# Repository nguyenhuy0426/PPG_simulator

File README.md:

# 🫀 PPG Signal Simulator — Raspberry Pi 4

**Dual-channel PPG research simulator with Raspberry Pi software, three KiCad 10 boards and a printable optical enclosure.**

**Group #2:** HuyNN, VyPT
**Institution:** Industrial University of Ho Chi Minh City (IUH) — Faculty of Electronic Technology
**Version:** 5.0.0 — waveform controls and timestamped recording

---

## 📋 Overview

The Raspberry Pi runtime synthesizes IR/RED signals at 100 Hz, interpolates them
for a nominal 500 Hz dual-MCP4725 output on ARM64, and acquires OPT101 signals separately.
`PPG_DAC_RATE_HZ` supports 100/200/500/1000 Hz; desktop default is 1000 Hz.
Pi GUI + BLE + A0 verification at 500 Hz completed 30 seconds without buffer
overruns or dropped samples. Optical waveform fidelity is still unverified.
The empirical SpO₂ mapping is configurable; a realistic plot does not establish
optical accuracy or compatibility with a particular pulse oximeter.

**Touch and sequence update (30 September 2026):** Numeric controls use sliders;
Settings and calibration include −/+ fine steps. **04 PPG morphology** offers
fitted Gaussian and an exploratory **LSM-GAN 30-second sequence**, a real training
reference, and a live **OPT101 RX** card (A0/A4).
Play/Stop uses the shared MCP4725 writer; clips stop at 30 seconds or when leaving
the page. Opening the page does not emit output. Classic Gaussian is preserved.

LSM keeps native 40 Hz timing and has no HR/notch conditioning. The existing v2
checkpoint has excessive beat variability relative to median validation data;
it is a development baseline, not a validated human-PPG replacement. IR/RED share
one shape with nominal scaling. See [architecture choice, measured sequence audit
and touch/output details](docs/ppg_touch_sequence_output_2026-09-30.md).
The [earlier morphology comparison](docs/ppg_morphology_selection_2026-09-28.md)
remains a historical exploratory result; test has already been viewed.

**RX beside TX & Bench Diagnostics (October 2026):**
- **Live A0/A4 RX card on every page:** Classic, Calibration, Recordings and PPG morphology each show a read-only RX card next to the TX plot (the earlier bottom dock, and the RX strip inside the Signal setup window, are removed). It displays the rolling 8-second window of raw ADC mV at up to 10 Hz refresh, with explicit status states (disabled, dry-run, stale, error, full-scale) and touch-optimized scrolling on 1024×600 screens ([docs/rx-monitor-2026-10-01.md](docs/rx-monitor-2026-10-01.md)).
- **Physical Sensor Diagnostic Protocol:** A bench test and signal conditioning plan is established for OPT101 / CJMCU-101 modules, covering internal 1 MΩ feedback verification, 3.3 V Grove Hat input limits, dark readings, stepped sine wave tests (1–10 Hz), and RC low-pass filtering at $f_c \approx 33.9\text{ Hz}$ ([docs/opt101-a0-diagnostic-2026-10-01.md](docs/opt101-a0-diagnostic-2026-10-01.md)).

| Live monitor | Waveform setup | 30-second sequence |
|---|---|---|
|  |  |  |

### What's complete in v5

- Light controls, charcoal IR/RED plots, large setpoints and timestamp axes. The UI scales automatically from compact 7-inch 1024×600 panels through Full-HD/QHD desktop displays.
- HR 10–300 bpm; respiration 1–150 brpm; SpO₂ target 0–100%; PI convenience input 0.01–30%.
- Independent IR/RED AC and DC, AC/DC ownership, output offset, gain and polarity.
- PPG, sine, triangle and square waveforms; independent SP/DN/DP timing for each channel.
- Baseline, amplitude and frequency respiratory modulation, inhale/exhale ratio, per-channel variation and periodic apnea.
- Absolute-mV artefacts with optional seeds; configurable HR/amplitude, SpO₂/notch and beat-variability effects.
- Timestamped 100 Hz model-command CSV recording continues across pages; playback follows the recorded timestamps.
- Explicit Start/Stop for calibration; only the engine's DAC thread produces its sine output.
- Configuration round-trip, validation and atomic JSON save. Opening a page does not change signal parameters.
- English/Vietnamese UI; touch-sized controls; TX on the left and live OPT101 A0/A4 RX on the right of every page.
- Collapsible left navigation rail (icons collapsed, labels overlay when expanded), light/dark theme saved in `config.json`, and a Classic page with TX and RX side by side. The status line reports *no MCP4725 at 0x60/0x61* instead of claiming LED output when the DACs do not answer.
- `scripts/deploy_and_run.sh` (run on the laptop): SSH check, `i2cdetect -y 1` report for 0x08/0x60/0x61, rsync to the Pi, restart the app on the Pi display (the autostart user service when it is installed), and a dry-run copy on the laptop. When the Ethernet link reports `NO-CARRIER`, use the Wi‑Fi address: `PI_HOST=user@<pi-wifi-ip> scripts/deploy_and_run.sh`, and stop any other running instance first so two apps do not share I2C/BLE.

See [the continuation and validation report](docs/phase_reports/V5_CONTINUATION_REPORT.md)
for scope, evidence, commercial-reference comparison and physical validation still needed.

### Neural waveform models

The app's Neural page offers the fitted three-Gaussian shaper and the LSM-GAN sequence (normalized 30 s strip at 40 Hz,
BIDMC, no rate control, no paired IR/RED, no calibrated SpO₂); `assets/neural/manifest.json` lists the packaged files.

PhysioMix (round 9) and PhysioFlow (round 10) were removed from the app with every research generator that did not
improve on them. A strict real-vs-generated judge retrained per source on unseen people (C2ST, validation AUC; 0.5 =
indistinguishable, the real-vs-real control is about 0.45) still separated them at 0.99–1.00, as it did PhysioMix with
the strict critic, LSM-GAN-S, the flow-GANs G1–G3, BeatGen and the spectral-finish variants (0.95–1.00). Kept for
further work: PhysioFlow-R (R1, mean 0.759 over seeds 0.745–0.785 at 16 Heun steps, the only clear gain), its fine-tune R1F and PhysioGAN-R
(P5, in training), and the LSM-GAN author topology as the unchanged baseline. The removed models' results stay in
`ml/runs`, [docs/model-report](docs/model-report/README.md) and [docs/physioflow/REPORT_VI.md](docs/physioflow/REPORT_VI.md);
their code is in git history. These are engineering evaluations of normalized waveform shape, not clinical
validation, and they were not measured on the Pi/DAC/OPT101.

PPG-physiGPT (`ml/kaggle_physigpt/`, research only, not in the app) is an unconditional GPT-PPG-style patch
transformer with a flow-matching head, pretrained on MIMIC-III WDB on Kaggle 2 x T4. The strict judge still separates
every variant (AUC 1.0). On a second, feature-level tier (1 - KS over 14 waveform features against unseen people),
the 99.9M large model reaches 0.941 against 0.933 for the best 30.7M base, where real people score 0.960. It is the
V1 release: V1 asks for 95% of the real-vs-real similarity (large: 98.1%). The V2 target, absolute 0.95 with a
feature-only tree classifier at most 0.60 accurate (large: 0.618), is not met; the gap left is 5-8 Hz detail. Results and run records: [docs/physigpt](docs/physigpt/README.md).

#### Earlier models (history)

The **04 PPG morphology** page keeps the original three-Gaussian
generator and offers the LSM-GAN sequence as an experimental model. The
cWGAN-GP checkpoint below is retained for research comparison; it is not the
current sequence source. Both neural models were trained from BIDMC 1.0.0 PPG
records using subject-separated train/validation/test groups. They do not learn
separate IR and RED optical channels.

| Model | What goes in → what comes out | Network idea | Current role |
|---|---|---|---|
| cWGAN-GP pilot | 32-value random latent vector + 7 measured morphology conditions → one 256-point, phase-normalized pulse | Dense layers followed by three linear-upsample/Conv1D stages; strided-convolution critic; Wasserstein loss with gradient penalty | Research artifact only; the pilot export contains G but not its trained critic. The app's older preview repeated this one pulse to form a longer trace. |
| LSM-GAN v2 | A random 1,200-point noise strip → 1,200 PPG samples, 30 s at 40 Hz | Generator has parallel Conv1D branches (kernels 5/21/61) and a spectral-matching objective; its discriminator is a CNN with two real/fake scores | Experimental long-sequence option in page 04; no HR/notch control. |

For LSM-GAN, training used 624 non-overlapping 30-second windows from 32
patients; validation and test each used 112 windows from 7 separate patients.
BIDMC's 125 Hz signals were resampled to 40 Hz, filtered at 0.9–5 Hz and
normalized per window. This is not raw, full-band PPG or a healthy-population
dataset. The model produces a normalized shape; the app maps that shape to
nominal IR/RED voltage levels, so it does not predict two independently learned
optical signals or calibrated SpO₂.

These experiments are **exploratory** because the test set had already been
viewed. cWGAN makes a single pulse while LSM-GAN makes a long sequence, so
their scores are not a fully like-for-like ranking. Selection considers the
pre-agreed spectrum similarity, autocorrelation and high-frequency energy;
loss and discriminator scores alone are not evidence of realistic PPG.
See the [detailed LSM/GAN report](docs/ppg_lsm_gan_report_2026-09-26.md),
[cWGAN and LSM integration audit](docs/ppg_neural_preview_report_2026-09-28.md)
and [current sequence and hardware validation](docs/ppg_touch_sequence_output_2026-09-30.md).

### Key Specifications

| Parameter               | Value                                           |
|------------------------|-------------------------------------------------|
| Platform               | Raspberry Pi 4 (Ubuntu 24.04/26.04 LTS, arm64)  |
| UI Library             | CustomTkinter                                   |
| DAC                    | MCP4725 (12-bit, I2C) × 2 — IR & Red channels   |
| Model Rate             | 100 Hz                                          |
| DAC Rate               | Pi: 500 Hz target; configurable; Linux/I²C timing requires measurement |
| Data Recording         | 100 Hz model commands, timestamped CSV in `dataset/` |
| DAC Voltage Range      | Configured 0–3.28 V (0 → 0, 3.28 V → 4095) |
| Live RX ADC Channels   | A4 (IR) & A0 (Red) on Grove Base Hat (I2C 0x08) |

---

## 🛠️ Hardware Architecture

### Pin Mapping (Raspberry Pi 4, BCM numbering)

```
MCP4725 DACs (I2C Bus 1):
  GPIO2 (pin 3)   → I2C1_SDA
  GPIO3 (pin 5)   → I2C1_SCL
  Addresses: 0x61 (IR channel), 0x60 (Red channel)

Display:
  HDMI → Any screen (auto-detect resolution)
```

### Official KiCad PCB design

The official panel contains **two electrically independent boards**: the
70 × 20 mm OPT101 receiver and the 70 × 40 mm LED/IR driver. The 70 × 60 mm
panel has one V-score at 20 mm from the top. BPW34 remains available as a
separate historical alternative and is not part of this panel.

- [Two-board panel and build instructions](hardware/ppg_panel/README.md)
- [LED/IR driver schematic, PCB and wiring](hardware/led_ir_driver/README.md)
- [OPT101 receiver](hardware/opt101_receiver_kicad/opt101_receiver/README.md)
- [BPW34 receiver (alternative)](hardware/bpw34_receiver/README.md)

The driver uses a single shared I²C connection: J2 pins 3–6 are SCL, SDA,
3.3 V and GND. Both MCP4725 modules share that bus; configure different
addresses (IR 0x60 and RED 0x61). J2 pins 1–2 are the IR DAC output and GND,
not part of the four-wire I²C cable. J2 uses a 2.54 mm 1×2 header and a
separate 2.00 mm 1×4 header. There are no J8/J9 I²C headers or R11–R14 /
JP1–JP4 I²C options on this design. See the driver README before wiring.

This restores the earlier shared-bus driver; later v2.0 manufacturing-rule
changes are not incorporated. Existing three-board panel and v2.0 driver
fabrication files are obsolete and have been removed. Recheck board-house
requirements and regenerate Gerber/drill files before ordering. CAD checks do
not establish physical operation.

### Printable optical enclosure

The dark chamber has separate RED/IR lanes, a sliding LED carrier, replaceable
apertures, a labyrinth lid and cable passages. The parametric model and assembly
instructions are in [docs/system_3d](docs/system_3d/README.md). For a 180 mm
Bambu bed, use the [three-plate print package](docs/system_3d/out/print_bambu_180.zip)
for the original enclosure parts. The compact receiver PCBs use **separate H-shaped
supports**, with open space under the PCB for header cables: [OPT101 STL](docs/system_3d/out/print_bambu_180/14_ga_chu_U_OPT101_70x20.stl)
and [BPW34 STL](docs/system_3d/out/print_bambu_180/15_ga_chu_U_BPW34_70x20.stl).
The driver has its [70 × 40 mm adapter STL](docs/system_3d/out/print_bambu_180/16_ga_driver_70x40.stl).
Read the [mounting notes](docs/system_3d/out/print_bambu_180/README_PCB_MOUNTS.md)
before printing: the receiver support is 3.8 mm thick in a 4.3 mm nominal slot;
test-print one support and check fit in the actual enclosure.

KiCad ERC/DRC, schematic-to-PCB checks and nominal mechanical collision checks
are recorded in each hardware project's `reports/` and `mechanical/` folders.
They do not establish physical fit, analog noise, optical isolation or LED current.
Check module pin order, MCP4725 I²C addresses, supply voltage and fit on the
actual parts before powering the assembly.

> **The IR lane has no STLs of its own — this is deliberate, not a missing
> export.** The two optical lanes are mirror-symmetric about z = 0, so the
> `slide_shaft`, `led_carrier`, `push_rod`, `rod_knob`, `aperture_*` and `hood_*` parts are
> exported once under the `_red` name and printed twice (the `*_ir` copies exist
> in `model.json` for the viewer only). Print counts are in the STL table of the
> `docs/system_3d/` README.

---

## 💻 Software Architecture

### Folder Structure

```
PPG_simulator_raspi/
├── main.py                      # Application entry point
├── config.py                    # Constants, theme & styles (single source of truth for version)
├── config_store.py              # JSON configuration persistence & validation
├── core/
│   ├── signal_engine.py         # Signal generation thread & DAC output
│   ├── csv_logger.py            # Dataset recording logic
│   ├── tx_rx_logger.py          # Paired TX command & RX acquisition logger
│   └── rate_scheduler.py        # Drift-free fixed-rate execution ticker
├── hw/
│   ├── opt101_rx.py             # Grove Base Hat ADC reader (A0/A4 channels)
│   └── dac_manager.py           # Dual MCP4725 I2C DAC controllers
├── models/
│   ├── ppg_model.py             # PPG physiological synthesis model
│   ├── noise.py                 # Artefact generators (absolute-mV, band-limited)
│   ├── respiration.py           # Respiratory baseline/amplitude/RSA modulation
│   ├── waveform.py              # Pulse morphology (Gaussian, sine, square, triangle)
│   └── limits.py                # Parameter limits and boundary validation
├── led_driver/                  # Op-amp + BJT current-sink calculations & error budget
├── ui/
│   ├── ctk_app.py               # Main CustomTkinter UI shell & window manager
│   ├── rx_monitor.py            # Read-only A0/A4 RX lanes shown beside TX on every page
│   ├── trace_view.py            # High-performance trace plot widget
│   ├── touch_slider.py          # Touch-optimized slider with +/- step buttons
│   ├── advanced_controls.py     # Parameter validation & event dispatcher
│   ├── i18n.py                  # English and Vietnamese UI translations
│   ├── responsive.py            # Multi-resolution UI scaling (1024x600 to 4K)
│   └── frames/
│       ├── pathology_frame.py   # Classic PPG simulator & pathology controls
│       ├── calibration_frame.py # Sine wave DAC test & calibration
│       ├── advanced_frame.py    # Signal setup (AC/DC ownership, SpO2, artefacts)
│       ├── neural_frame.py      # LSM-GAN 30s sequence & morphology evaluation
│       └── playback_frame.py    # CSV recording browser & playback viewer
├── hardware/                    # KiCad 10 projects, V-cut panel & release ZIPs
├── docs/                        # Design documents, reports, and 3D STL models
│   ├── opt101-a0-diagnostic-2026-10-01.md # Bench test plan for physical sensor
│   ├── rx-monitor-2026-10-01.md           # Live RX view design notes & validation (dock era)
│   ├── ppg_touch_sequence_output_2026-09-30.md # Touch controls & GAN details
│   └── system_3d/               # 3D printable dark enclosure STLs & guide
└── dataset/                     # Recorded CSV dataset files
```

---

## 🔧 Installation & Setup

### 1. Prerequisites
- Raspberry Pi 4 with Ubuntu 24.04 or 26.04 LTS (aarch64)
- I2C enabled (`dtparam=i2c_arm=on` in `/boot/firmware/config.txt`; the setup
  script can add it after confirmation)
- Python 3.10+ and OS package `python3-tk`; install dependencies inside a venv.

For Ubuntu, use the repository setup script instead of installing into the
system Python:

```bash
./scripts/setup_rpi_ubuntu.sh --enable-i2c
```

For a laptop-to-Pi Ethernet cable, source transfer, repeatable `ping`/`ssh`
commands, and remote debugging, follow
[docs/setup/RASPBERRY_PI_4_UBUNTU_26_04_SSH.md](docs/setup/RASPBERRY_PI_4_UBUNTU_26_04_SSH.md).

### 2. Laptop setup, run and tests

```bash
python3 -m venv .venv
.venv/bin/python -m pip install --upgrade -r requirements/test.txt
.venv/bin/python main.py --dry-run
PPG_DRY_RUN=1 .venv/bin/python -m pytest -q
```

On the configured Raspberry Pi, use `.venv/bin/python main.py` for hardware mode.
Virtual environments are deliberately excluded from Git; recreate one on each
machine because wheels and interpreter paths are architecture-specific.

GUI interaction and screenshot check (requires a real display or Xvfb):

```bash
.venv/bin/python scripts/smoke_ui.py --output docs/ui
```

Install the PPG Simulator icon in the Raspberry Pi application dashboard and
place a trusted shortcut on the desktop:

```bash
./scripts/install_desktop_launcher.sh
```

The launcher uses this checkout's `.venv`, starts the normal GUI with BLE
and writes startup logs to `~/.local/state/ppg-simulator/launcher.log`.
`main.py` itself allows one instance per user, however it was started: a
second copy, including `--dry-run` and `--ble-only`, exits with status 75 and
names the process that holds `~/.local/state/ppg-simulator/app.lock`.

For a standalone bench, install the systemd user service. It starts the
simulator with the Pi's desktop session and restarts it after a crash; once it
is installed, the icon starts that service. Automatic login, the restart limits
and the commands are in
[setup guide §11](docs/setup/RASPBERRY_PI_4_UBUNTU_24_04.md#11-start-automatically-with-the-desktop-session):

```bash
./scripts/install_user_service.sh --now
```

The laptop environment verifier also audits Git hygiene and rejects committed
virtual environments, bytecode and generated package caches.

### 3. BLE remote control (Android app)

The simulator can be driven from the Android app (`com.medical.simulator`)
over BLE GATT: `pip install -r requirements/ble.txt`, then run with `--ble`
(GUI) or `--ble-only` (headless). The phone advertises-pairs as central, sends
JSON setpoint commands (HR/SpO₂/RR/PI/noise/condition plus AC/DC amplitude
0–1500 mV per channel) and receives the 50 Hz waveform plus a 5 Hz status
snapshot with bidirectional sync. Full contract: `docs/ble_protocol.md`.

```bash
PPG_DRY_RUN=1 .venv/bin/python main.py --dry-run --ble        # GUI + BLE
PPG_DRY_RUN=1 .venv/bin/python main.py --dry-run --ble-only   # headless
```

---

## Operation

**Monitor:** adjust HR, SpO₂ target, respiration and PI with sliders, or type a
value and press Enter. Run starts TX; Stop parks both DAC command values at zero.
Record CSV starts capture; Save recording closes the file into `dataset/data_N.csv`.
Closing the app saves an active recording. The plotted signal is generated TX,
not an optical measurement. The right-hand numbers are setpoints.

**Signal setup:** each tab applies only when its Apply button is pressed.
Blank RED AC derives it from SpO₂. Explicit RED AC disconnects that amplitude
from the SpO₂ target and the monitor reports this. Lock AC holds AC while a PI
change moves IR DC; Lock DC lets PI move AC; both locks make PI read-only.
Feature times are quoted at 60 bpm and scale with cycle duration.

For a repeatable nominal waveform, disable respiratory modulation and all three
physiological dynamics switches on the Respiration tab. Otherwise modulation,
HR coupling and beat variability deliberately change the instantaneous AC/HR.

**Calibration & Sine Generator:** enter sine frequency (1–10 Hz) and peak output (100–3280 mV),
then Start calibration. Opening the page alone does not start output. Leaving the
page stops an active calibration. Sine calibration drives both MCP4725 DAC channels simultaneously.

**Optical operating levels (after moving an LED carrier or the receiver):** each
LED→OPT101 path has its own gain, turn-on and ceiling. On 2026-11-14 the IR
driver stopped adding current above ~0.6–0.75 V DAC (~3 mA) and the OPT101
outputs topped out at ~2.5 V (datasheet minimum at 3.3 V: 2.0 V). Drive past
the IR knee made the IR reading fall for seconds; that, not the ADC or the UI,
clipped the old Calib sine. See docs/hardware-validation/2026-11-14-ir-overload.

**Calibration pass dots.** Set IR/RED levels (DAC mV), an optional ± sine and a
± tolerance, then Start. The dot beside each RX lane blinks green while the
OPT101 lane reads the sent level (or the sine peak/trough) within the
tolerance; the text shows the received value and Δ = received − sent. There is
no automatic optical compensation: a dot that stays red means that path's
optical gain or range differs, to be fixed in the optics or the levels.

**Live RX card:** every page shows an RX card to the right of its TX plot
(the Signal setup window has none). The receiver samples the Grove Base Hat ADC at 100 Hz and refreshes the UI at up to 10 Hz,
plotting an 8-second rolling window for A4 (IR) and A0 (Red). Sensor readings display raw
millivolts alongside real-time connection status (`LIVE`, `STALE`, `DRY RUN`, `DISABLED`, or `FULL SCALE`).
Dry-run mode and unplugged sensors explicitly show disconnected states without fabricating data.

**Neural Sequence & Morphology Evaluation:** the **04 PPG morphology** page allows selecting
between the standard three-Gaussian pulse synthesis and an experimental 30-second LSM-GAN
continuous pulse sequence. Clips automatically stop at 30 seconds or upon navigating away.
Opening the screen does not activate DAC output without an explicit Play action.
The TX card stacks the generated lane over the real reference lane; the RX card
on the right shows A0/A4 from the receiver.

**Recordings:** review saved TX command CSVs without driving hardware. The session
list is a drawer that folds to one icon and closes after a recording is picked.
Recorded TX sits on the left and the live RX card on the right; that RX is the ADC
reading at viewing time, not data stored in the recording. New files
contain `Time_s` and `Source`; the first seven columns retain the legacy schema.
Legacy files without timestamps explicitly assume 50 Hz for screen playback.
CSV output is a model command record, not proof that a DAC wrote every sample.

**Bench Diagnostics & Optical Validation:** for physical sensor testing with the OPT101 / CJMCU-101 module,
follow the testing protocol in [docs/opt101-a0-diagnostic-2026-10-01.md](docs/opt101-a0-diagnostic-2026-10-01.md):
1. Verify module pinout (ensure 1 MΩ internal feedback loop between pins 4 & 5; do not leave floating).
2. Measure baseline dark voltage under complete optical enclosure sealing.
3. Perform stepped sine excitation (1, 2, 5, 10 Hz) via DAC to measure sensor linearity, phase shift, and harmonic distortion.
4. If high-frequency ripple or ADC noise is present, insert an anti-aliasing RC filter ($R = 4.7\text{ k}\Omega$, $C = 1\ \mu\text{F}$, $f_c \approx 33.9\text{ Hz}$) between the OPT101 OUT pin and Grove A0 input. Keep Grove signals strictly $\le 3.3\text{ V}$.

| Calibration and RX status | Recording review |
|---|---|
|  |  |

## Signal relationships and limits

`PI = AC_IR / DC_IR × 100`; at DC=1500 mV, PI=3% gives nominal AC=45 mV.
RED is derived with the full ratio-of-ratios:

`R = max(0, (A − SpO₂_target) / B)`

`AC_RED = R × AC_IR × DC_RED / DC_IR`

The defaults A=110 and B=25 are an empirical example, not universal optical
calibration. The former R clamp of 0.4–1.6 has been removed so low SpO₂ targets
change the generated ratio. A negative requested R cannot be synthesized; the
monitor reports it. Unequal respiration depth and manually pinned RED AC can
change the instantaneous ratio from the nominal target.

PPG uses a normalized three-Gaussian shape. Respiratory depth defaults to 4% of
AC per channel, with baseline/amplitude/RSA modulation individually selectable.
Apnea suppresses respiratory modulation while cardiac pulses continue.

Direct AC entry spans 0–1500 mV and DC entry 0–1500 mV, matching the Android
app. PI-driven AC stays inside the direct AC range at these limits; output
offset spans 0–2000 mV with DC+offset≤3000 mV. Gain,
noise and modulation can still exceed DAC headroom: the output clamps to the
configured rails and the clipping counter reports it. A clipped waveform does
not meet the requested amplitude or ratio.

50/60 Hz mains noise is rejected by the 100 Hz synthesis model; 10× interpolation
does not create additional bandwidth. Likewise, the MCP4725 code step is about
0.80 mV at 3.28 V: software entry resolution is finer than physical DAC resolution.

The LED-driver topology in the supplied drawing is DAC → op-amp → NPN current
sink with emitter feedback through R_sense. The 3D preview defaults to this direct
command path, and offers the older 10k/10k divider hypothesis separately. Its
`I ≈ Vcmd/R` readout is an ideal estimate; current, compliance and optical response
must be measured on the actual assembly. No wiring, transistor or resistor is
changed by this software update.

## References

The datasheets, papers and web sources used by the hardware, PPG model and
neural-model work are collected in [docs/REFERENCES.md](docs/REFERENCES.md).

## 👨‍💻 Authors

**HuyNN** — Hardware design, embedded firmware  
**VyPT** — Software design, UI/UX

**Institution:** Industrial University of Ho Chi Minh City (IUH)

## Official PSF model (2026-11-12)

PSF J3 EMA step 5500 is the official project baseline. The CPU TorchScript bundle, checksum, runtime contract and comparison with J4/J5/J6 are documented in [assets/psf/README.md](assets/psf/README.md). This remains an experimental simulator: held-out similarity 94.94%, tree accuracy 66.625%; the global realism gate has not passed and clinical validation is absent. Future automatic evaluations report feature-classifier accuracy/AUC; historical results are preserved.

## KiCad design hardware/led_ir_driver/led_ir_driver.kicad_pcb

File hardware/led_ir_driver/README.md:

# LED/IR driver — official shared-I²C design

Open `led_ir_driver.kicad_pro` in KiCad 10. This 70 × 40 mm board restores
the v1.9 shared-bus design. It has two MCP4725 module sockets, an LM358 and
two independent LED current drivers. The official two-board panel is in
[`../ppg_panel/`](../ppg_panel/README.md).

## I²C wiring

J2 uses two separate headers: 1×2 at 2.54 mm for pins 1–2 and 1×4 at
2.00 mm for pins 3–6. Connect the four-wire Pi/Grove I²C cable to pins **3–6**:

| J2 pin | Signal |
|---|---|
| 1 | IR DAC output |
| 2 | GND |
| 3 | SCL |
| 4 | SDA |
| 5 | 3.3 V |
| 6 | GND |

J1 (IR) and J3 (RED) share SCL, SDA, 3.3 V and GND. Their DAC outputs are
separate. Set the modules to distinct addresses: IR `0x60`, RED `0x61`;
verify the module variant and ADDR solder links. Use 3.3 V on the I²C header,
not 5 V. The driver 5 V supply and Pi must share GND. Check the actual cable
pin order before connecting. J8/J9, R11–R14 and JP1–JP4 from v2.0 are absent.
Module pull-ups are in parallel; check the resulting bus electrically.

See [connectivity review](CONNECTIVITY_REVIEW.md), [pin map](PIN_MAP.md) and
[electrical audit](ELECTRICAL_AUDIT.md) for circuit details. These documents
correspond to the restored v1.9 source and include historical observations.

## Verification and fabrication

The restored driver passed KiCad ERC, PCB DRC and schematic parity checks.
The later v2.0 board-house changes (0.5 mm ground-pour clearance and 1.5 mm
I²C-header pads) have not been applied to this restored version. There is no
current manufacturing release: verify clearances, pad sizes, mechanics and
board-house requirements, then regenerate and inspect Gerbers and drills.
Check current, startup behavior and stability on assembled hardware; CAD
checks do not prove electrical operation. The MCP4725 may restore a nonzero
EEPROM output at startup.

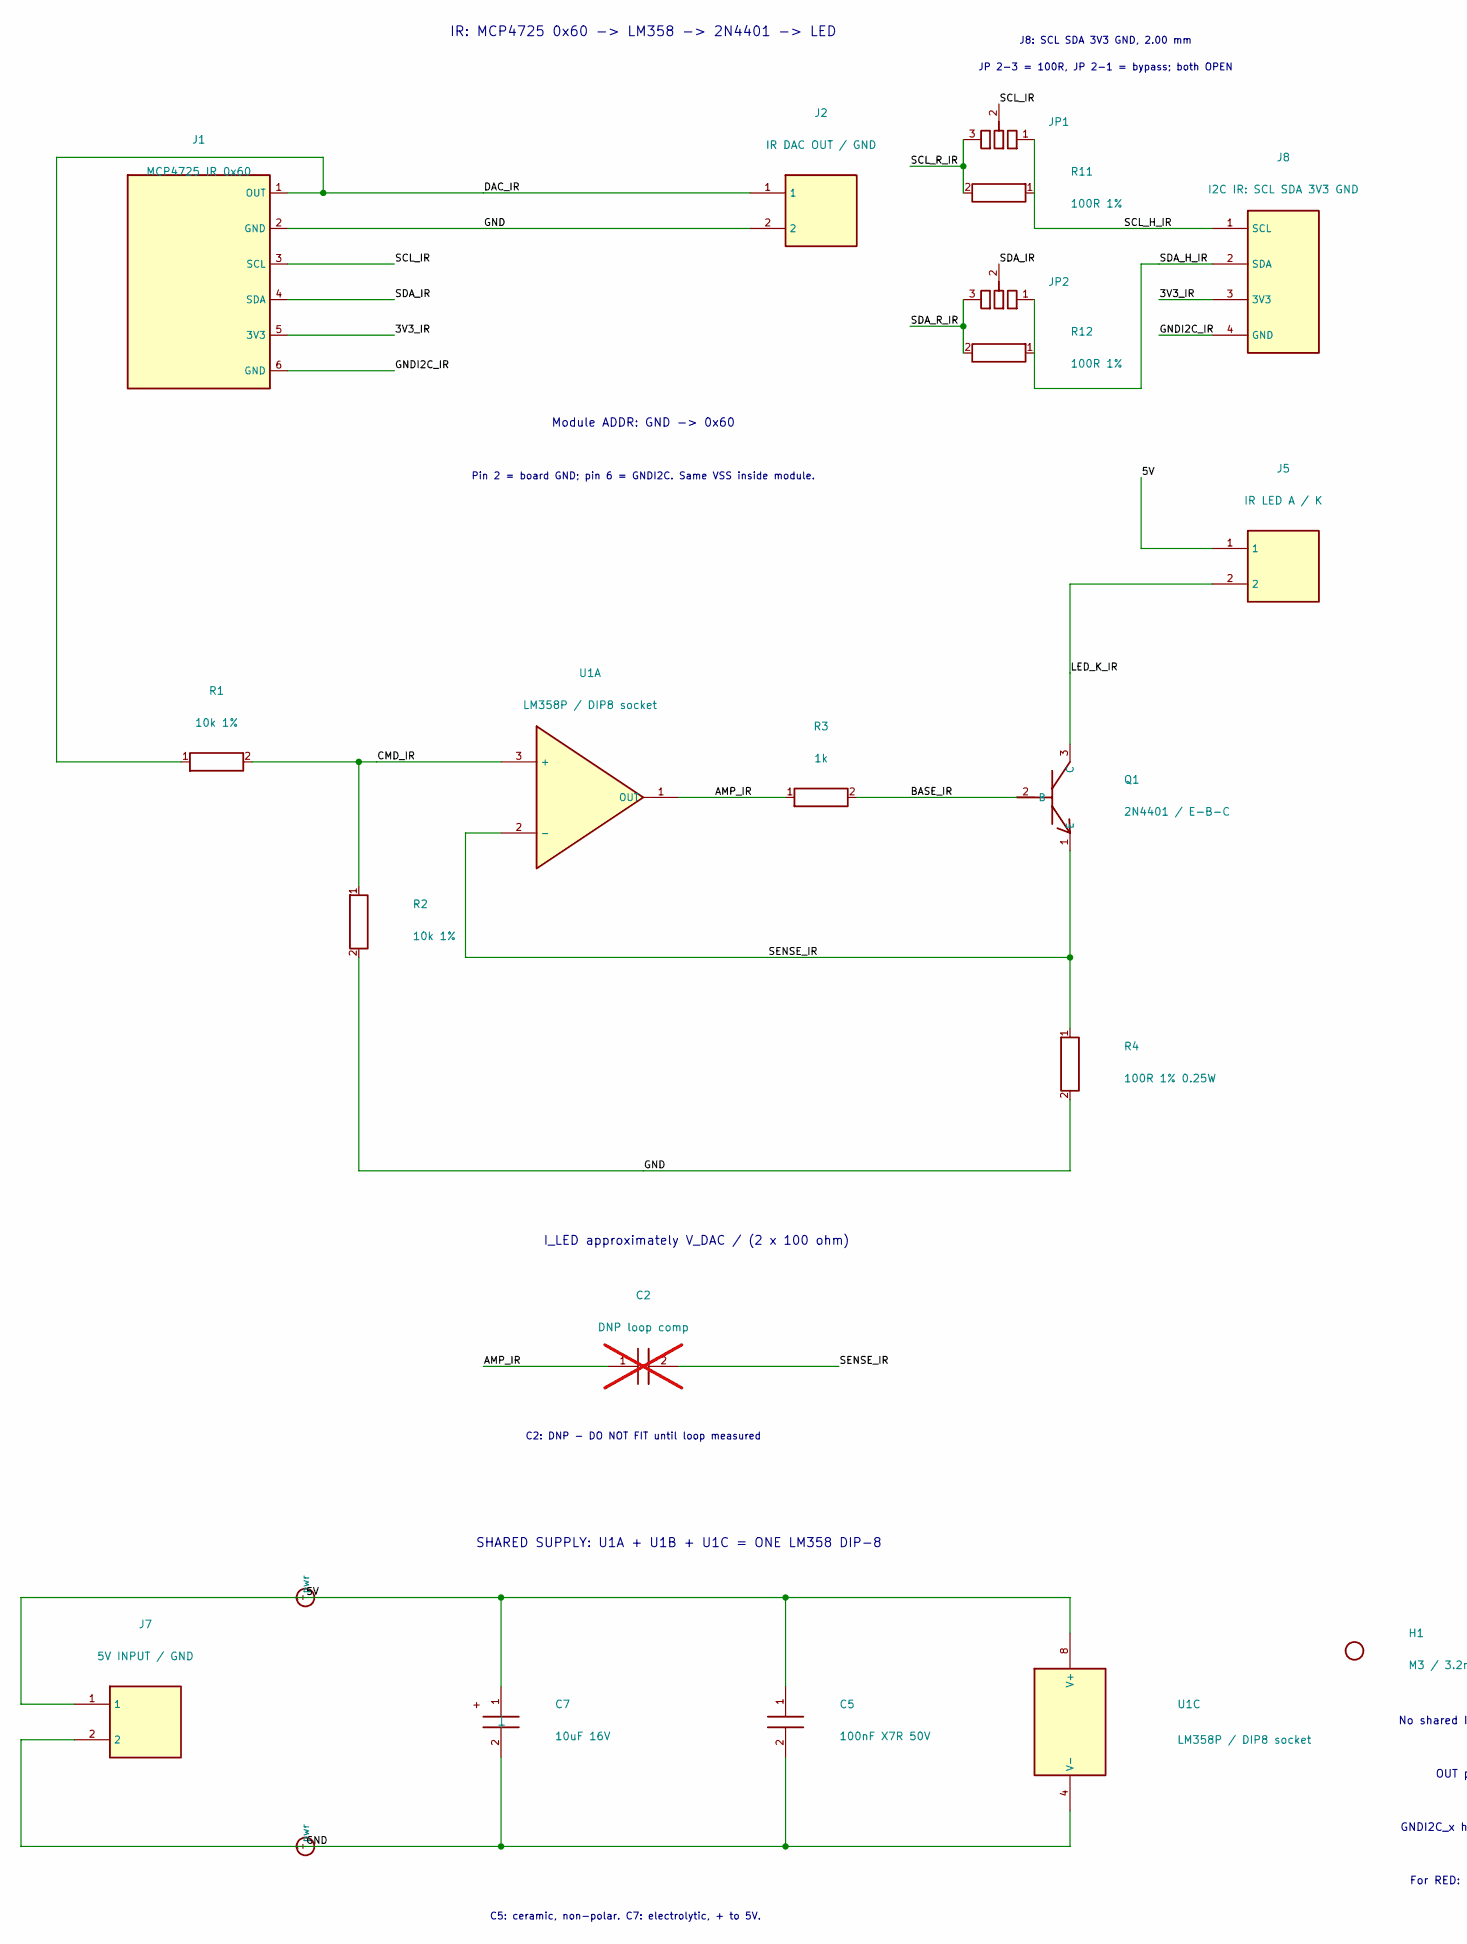
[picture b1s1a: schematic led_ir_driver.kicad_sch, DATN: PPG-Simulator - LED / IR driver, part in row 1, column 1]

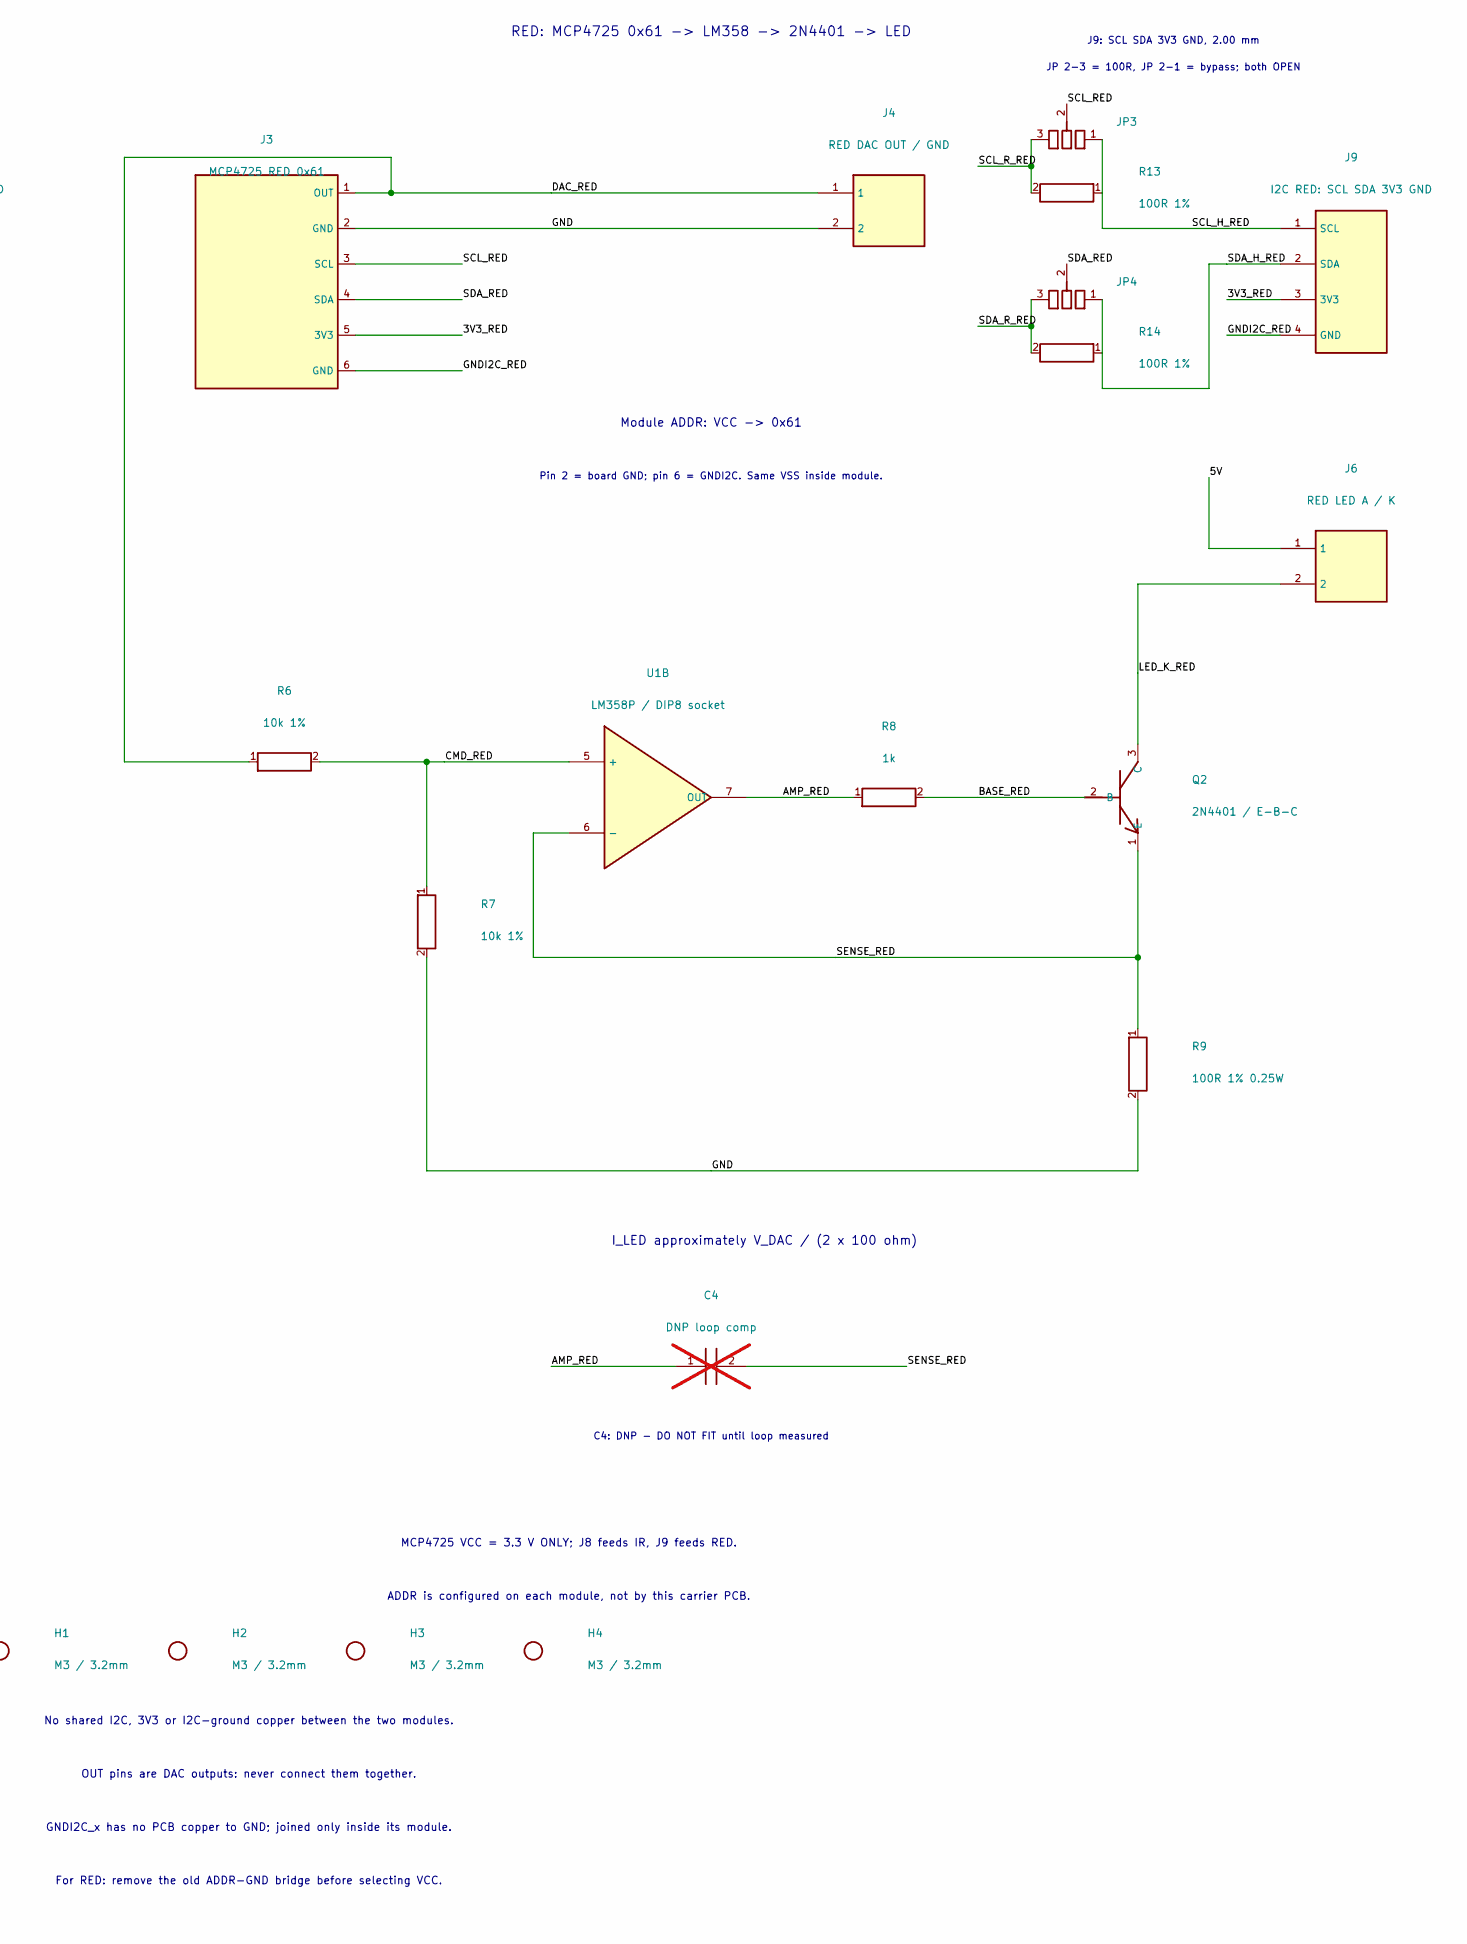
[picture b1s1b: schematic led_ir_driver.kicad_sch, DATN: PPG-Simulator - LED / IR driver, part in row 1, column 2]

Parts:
C2, C4: DNP loop comp; C; not fitted
C5: 100nF X7R 50V; C
C7: 10uF 16V; CP
H1, H2, H3, H4: M3 / 3.2mm; Hole
J1: MCP4725 IR 0x60; Socket6
J2: IR DAC OUT / GND; Header2
J3: MCP4725 RED 0x61; Socket6
J4: RED DAC OUT / GND; Header2
J5: IR LED A / K; Header2
J6: RED LED A / K; Header2
J7: 5V INPUT / GND; Header2
J8: I2C IR: SCL SDA 3V3 GND; Header4
J9: I2C RED: SCL SDA 3V3 GND; Header4
JP1: SCL IR 1-2 BYP / 2-3 100R; SJ3
JP2: SDA IR 1-2 BYP / 2-3 100R; SJ3
JP3: SCL RED 1-2 BYP / 2-3 100R; SJ3
JP4: SDA RED 1-2 BYP / 2-3 100R; SJ3
Q1, Q2: 2N4401 / E-B-C; NPN
R1, R2, R6, R7: 10k 1%; R
R3, R8: 1k; R
R4, R9: 100R 1% 0.25W; RSense
R11, R12, R13, R14: 100R 1%; R
U1: LM358P / DIP8 socket; DIP8

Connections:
/3V3_IR: J1.5 (3V3), J8.3 (3V3)
/3V3_RED: J3.5 (3V3), J9.3 (3V3)
/5V: C5.1, C7.1 (+), J5.1, J6.1, J7.1, U1.8 (V+)
/AMP_IR: C2.1, R3.1, U1.1 (OUT)
/AMP_RED: C4.1, R8.1, U1.7 (OUT)
/BASE_IR: Q1.2 (B), R3.2
/BASE_RED: Q2.2 (B), R8.2
/CMD_IR: R1.2, R2.1, U1.3 (+)
/CMD_RED: R6.2, R7.1, U1.5 (+)
/DAC_IR: J1.1 (OUT), J2.1, R1.1
/DAC_RED: J3.1 (OUT), J4.1, R6.1
/GND: C5.2, C7.2 (-), J1.2 (GND), J2.2, J3.2 (GND), J4.2, J7.2, R2.2, R4.2, R7.2, R9.2, U1.4 (V-)
/GNDI2C_IR: J1.6 (GND), J8.4 (GND)
/GNDI2C_RED: J3.6 (GND), J9.4 (GND)
/LED_K_IR: J5.2, Q1.3 (C)
/LED_K_RED: J6.2, Q2.3 (C)
/SCL_H_IR: J8.1 (SCL), JP1.1 (BYP), R11.1
/SCL_H_RED: J9.1 (SCL), JP3.1 (BYP), R13.1
/SCL_IR: J1.3 (SCL), JP1.2 (COM)
/SCL_RED: J3.3 (SCL), JP3.2 (COM)
/SCL_R_IR: JP1.3 (100R), R11.2
/SCL_R_RED: JP3.3 (100R), R13.2
/SDA_H_IR: J8.2 (SDA), JP2.1 (BYP), R12.1
/SDA_H_RED: J9.2 (SDA), JP4.1 (BYP), R14.1
/SDA_IR: J1.4 (SDA), JP2.2 (COM)
/SDA_RED: J3.4 (SDA), JP4.2 (COM)
/SDA_R_IR: JP2.3 (100R), R12.2
/SDA_R_RED: JP4.3 (100R), R14.2
/SENSE_IR: C2.2, Q1.1 (E), R4.1, U1.2 (-)
/SENSE_RED: C4.2, Q2.1 (E), R9.1, U1.6 (-)

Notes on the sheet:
IR: MCP4725 0x60 -> LM358 -> 2N4401 -> LED
J8: SCL SDA 3V3 GND, 2.00 mm
JP 2-3 = 100R, JP 2-1 = bypass; both OPEN
Module ADDR: GND -> 0x60
Pin 2 = board GND; pin 6 = GNDI2C. Same VSS inside module.
I_LED approximately V_DAC / (2 x 100 ohm)
C2: DNP - DO NOT FIT until loop measured
RED: MCP4725 0x61 -> LM358 -> 2N4401 -> LED
J9: SCL SDA 3V3 GND, 2.00 mm
Module ADDR: VCC -> 0x61
C4: DNP - DO NOT FIT until loop measured
SHARED SUPPLY: U1A + U1B + U1C = ONE LM358 DIP-8
C5: ceramic, non-polar. C7: electrolytic, + to 5V.
MCP4725 VCC = 3.3 V ONLY; J8 feeds IR, J9 feeds RED.
ADDR is configured on each module, not by this carrier PCB.
No shared I2C, 3V3 or I2C-ground copper between the two modules.
OUT pins are DAC outputs: never connect them together.
GNDI2C_x has no PCB copper to GND; joined only inside its module.
For RED: remove the old ADDR-GND bridge before selecting VCC.

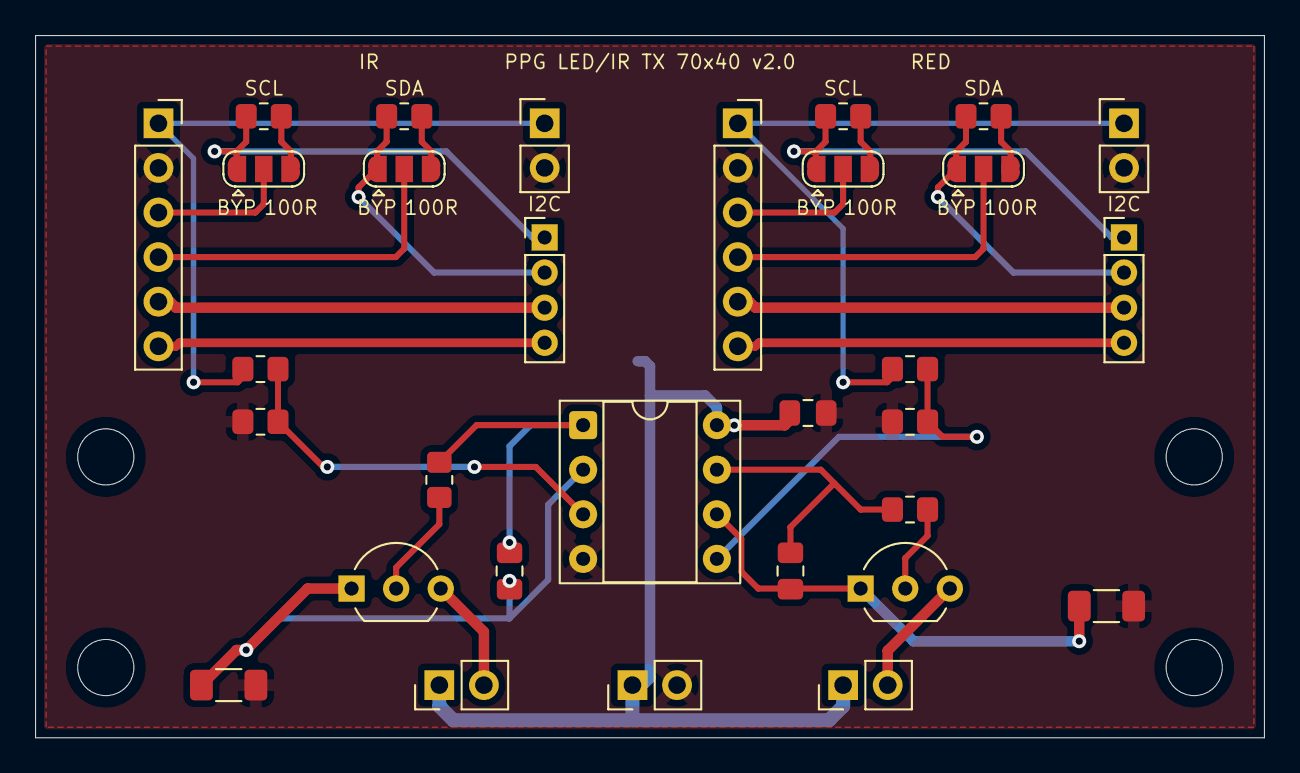
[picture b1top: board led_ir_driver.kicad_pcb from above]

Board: 2 copper layers, 70.0 x 40.0 mm, 36 parts (1 on the bottom side), 30 nets.

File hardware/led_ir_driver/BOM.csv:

Reference,Value,Footprint,Fit
J1,MCP4725 IR 0x60,TX:Socket6,YES
J3,MCP4725 RED 0x61,TX:Socket6,YES
J2,IR DAC OUT / GND,TX:Header2,YES
J8,I2C IR: SCL SDA 3V3 GND,TX:Header4,YES
R11,100R 1%,TX:R,YES
JP1,SCL IR 1-2 BYP / 2-3 100R,TX:SJ3,BRIDGE
R12,100R 1%,TX:R,YES
JP2,SDA IR 1-2 BYP / 2-3 100R,TX:SJ3,BRIDGE
J9,I2C RED: SCL SDA 3V3 GND,TX:Header4,YES
R13,100R 1%,TX:R,YES
JP3,SCL RED 1-2 BYP / 2-3 100R,TX:SJ3,BRIDGE
R14,100R 1%,TX:R,YES
JP4,SDA RED 1-2 BYP / 2-3 100R,TX:SJ3,BRIDGE
J4,RED DAC OUT / GND,TX:Header2,YES
U1,LM358P / DIP8 socket,TX:DIP8,YES
Q1,2N4401 / E-B-C,TX:NPN,YES
R1,10k 1%,TX:R,YES
R2,10k 1%,TX:R,YES
R3,1k,TX:R,YES
R4,100R 1% 0.25W,TX:RSense,YES
C2,DNP loop comp,TX:C,DNP
J5,IR LED A / K,TX:Header2,YES
Q2,2N4401 / E-B-C,TX:NPN,YES
R6,10k 1%,TX:R,YES
R7,10k 1%,TX:R,YES
R8,1k,TX:R,YES
R9,100R 1% 0.25W,TX:RSense,YES
C4,DNP loop comp,TX:C,DNP
J6,RED LED A / K,TX:Header2,YES
J7,5V INPUT / GND,TX:Header2,YES
C5,100nF X7R 50V,TX:C,YES
C7,10uF 16V,TX:CP,YES
H1,M3 / 3.2mm,TX:Hole,YES
H2,M3 / 3.2mm,TX:Hole,YES
H3,M3 / 3.2mm,TX:Hole,YES
H4,M3 / 3.2mm,TX:Hole,YES

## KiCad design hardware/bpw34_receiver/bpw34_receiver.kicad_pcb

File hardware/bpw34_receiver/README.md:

> Gá mới: thanh chữ U không bắt vít, hai biến thể riêng theo receiver. Xem `mechanical/README.md`.

# Dual BPW34 receiver for DATN: PPG-Simulator

This is a complete KiCad 10 project for a 70 x 20 mm, two-channel photodiode receiver that can replace the dual-OPT101 board mechanically. The optical centres remain 38.5 mm apart. The new screwless U support shares the enclosure slot; PCB mounting holes are removed.

## Electrical design

Each channel is independent and contains one BPW34, one OPA333 transimpedance amplifier, a 1 Mohm feedback resistor, and a 22 pF C0G/NP0 feedback capacitor. A 100k/10k divider creates a filtered 0.30 V reference from the 3.3 V Grove supply. Light-induced reverse current therefore raises the output:

`VOUT approximately 0.30 V + IPD x 1 Mohm`

R3/R4 = 1 kohm and C7/C8 = 1 uF X7R 16 V form an output low-pass filter (159 Hz nominal). The capacitor connects after the resistor to its channel ground. Attenuation at 20 Hz is approximately 0.8%; this is not a 50 Hz notch filter. C1/C2 are C0G/NP0 because their value sets TIA stability; C3-C6 are non-polar 100 nF X7R ceramic capacitors. No electrolytic capacitor is required.

The preferred amplifier is `OPA333AIDBVR` in SOT-23-5. The lower-cost `MCP6001T-I/OT` has the same pinout and footprint, but higher offset and drift. The board does not support LM358 because its input/output headroom is a poor match for a 3.3 V photodiode TIA.

The schematic now draws R1/C1 and R2/C2 as two visible parallel feedback branches between each BPW34 cathode (SUM) and the OPA333 output (FB). A supply arrow marks each channel's `3V3_RED` or `3V3_IR` net; a ground symbol marks `GND_RED` or `GND_IR`. The two channel grounds remain separate. The former diamond-shaped `PWR_FLAG` symbols have been removed; the Grove connector power pins are declared as the external source for KiCad ERC.

## Connectors

| Connector | Pin 1 | Pin 2 | Pin 3 | Pin 4 |
|---|---|---|---|---|
| J1, Grove A2 | OUT_RED | NC | 3V3_RED | GND_RED |
| J2, Grove A0 | OUT_IR | NC | 3V3_IR | GND_IR |
| J3, ADS1115 | OUT_RED | GND_RED | OUT_IR | GND_IR |

J1 and J2 are 1x4 male headers with 2.00 mm pitch. J3 is a 1x4 male header with 2.54 mm pitch. J3 intentionally carries no supply; power the ADS1115 normally and connect both J3 ground pins to its GND. The channel grounds remain separate on this PCB and meet at the HAT or ADS1115.

The Grove Base Hat must be configured for 3.3 V. Pin 2 of each Grove connector is deliberately unused.

## BPW34 polarity

Pad 1 is the cathode (`K`) and is square. Pad 2 is the anode (`A`) and is round. Match the BPW34 cathode marking to `K`; reversing the diode changes the bias and output polarity.

## Manufacturing and assembly

- 2 layers, FR-4, 1.6 mm, 70 x 20 mm.
- Solder D1/D2 and the three headers on the front.
- Solder U1/U2 and all 0805 parts on the rear.
- The rear components are arranged as two channel blocks: the feedback pair is
  in the upper row, the OPA333 and 1 kohm output path are in the middle, and
  the VREF divider is in the outer column. All reference designators read
  horizontally from the rear.
- The high-impedance `SUM_RED`, `SUM_IR`, `FB_RED`, and `FB_IR` routes remain
  on B.Cu and are kept local to their channel. The long supply/output runs use
  the opposite layer where needed, so they do not cut through the TIA loops.
- Every routed copper segment on F.Cu and B.Cu is horizontal, vertical or 45 degrees; the
  layout intentionally contains no diagonal track segments.
- Receiver mounting holes are removed; no copper crosses a drilled mounting opening.
- Both sides carry pin markings. On the rear, every J1/J2/J3 pad is labelled
  individually with an abbreviation; the nearby legend
  defines `R=OUT_RED`, `I=OUT_IR`, `V=3V3`, `N=NC`, and `GR/GI=channel GND`.
  D1/D2 also show `K` and `A`. Pin numbers are deliberately omitted from the
  rear labels. Read the mirrored rear silkscreen while
  looking directly at the rear.
- Fit the 22 pF parts as C0G/NP0, not X7R.
- Trim through-hole leads on the rear to at most 2 mm for the slide-in frame.
- If the output sits near 3.3 V under normal illumination, replace R1/R2 with 330 kohm. Do not parallel the RED and IR outputs.

## Generated evidence

- `reports/erc.rpt`: schematic electrical-rule check.
- `reports/drc.rpt`: PCB DRC, unconnected-item and schematic-parity check.
- `reports/pin_contract.json`: exact net/pin and mechanical contract audit.
- `reports/schematic.pdf` and `reports/schematic.png`: readable schematic.
- `reports/pcb_top.png`, `reports/pcb_bottom.png`: PCB renders.
- `reports/wiring_guide.png`: routing and pad-number guide.
- `fabrication/`: Gerbers and plated/non-plated drill files.
- `mechanical/`: adapter STLs, collision report and nominal optical report.

The CAD checks do not prove analog gain, noise, optical leakage, print shrinkage or physical fit. Measure the real LED current/output and perform a dark-box leakage test before ordering a large batch.

## Compact mechanical revision v1.4

Use `mechanical/frame_70x20_bpw34_print.stl`; see mechanical/README.md.

## Bố trí bản thu gọn hiện tại

PCB 70 × 20 mm, không có lỗ bắt vít. Tâm BPW34 tại (15,75;11,7)/(54,25;11,7) mm; hàng header Y=16,667 mm. Tất cả R/C ở mặt sau. Đường đồng ngang/dọc, vòng SUM và hồi tiếp giữ ngắn. Dùng riêng gá BPW34 có bậc Y thế giới=23,7 mm để giữ trục quang Y=32 mm; không dùng gá OPT101. Các bảng vị trí cũ được thay bởi tọa độ PCB và fit_report.json hiện tại.

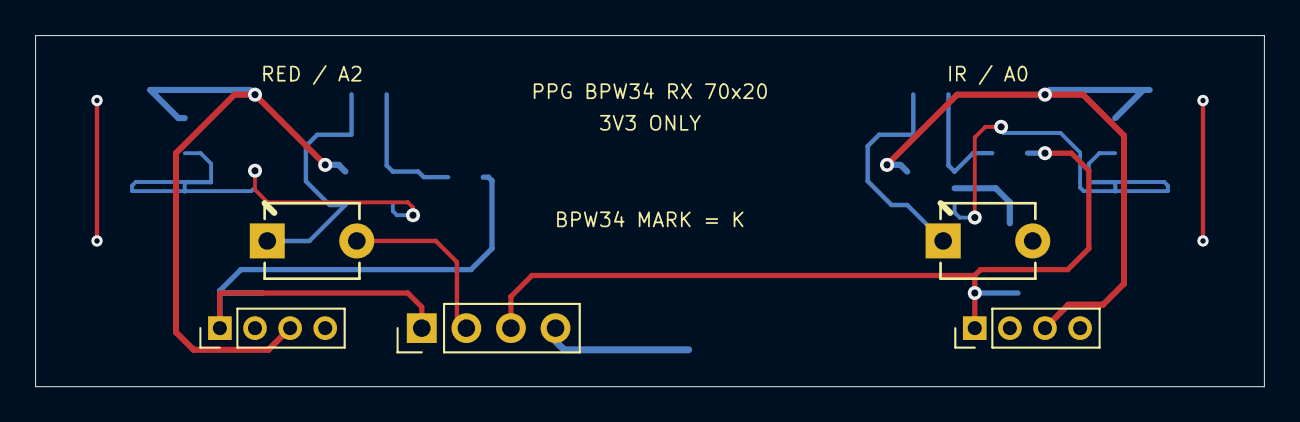
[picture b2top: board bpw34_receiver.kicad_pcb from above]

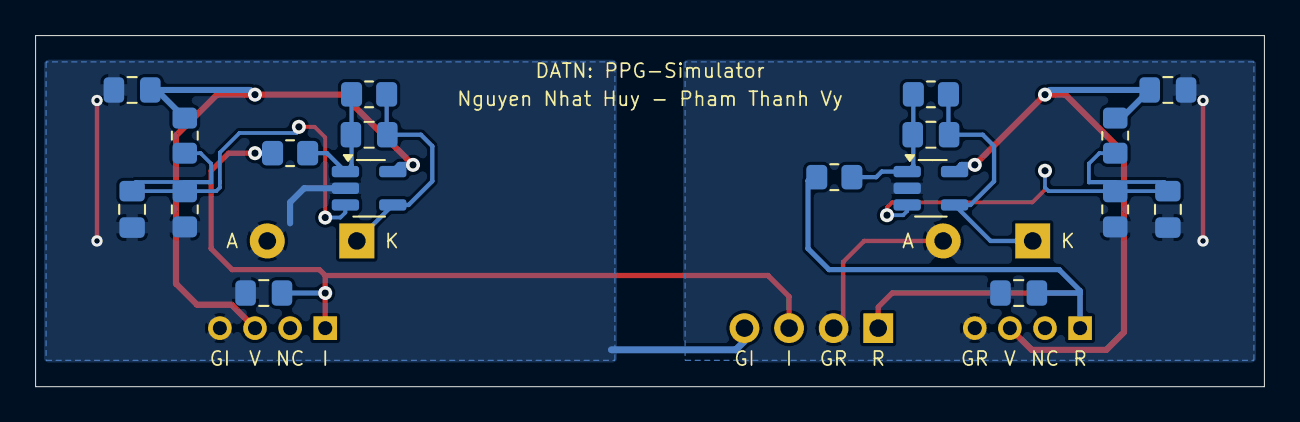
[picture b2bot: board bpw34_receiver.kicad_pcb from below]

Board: 2 copper layers, 70.0 x 20.0 mm, 23 parts (18 on the bottom side), 12 nets.

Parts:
C1, C2: 22pF C0G; C0805_Hand
C3, C4, C5, C6: 100nF X7R; C0805_Hand
C7, C8: 1uF X7R 16V; C0805_Hand
D1: BPW34 RED; BPW34_THT
D2: BPW34 IR; BPW34_THT
J1: A2 / RED; Header_1x04_P2mm
J2: A0 / IR; Header_1x04_P2mm
J3: ADS1115: RED/GND/IR/GND; Header_1x04_P2.54mm
R1, R2: 1M 1%; R0805_Hand
R3, R4: 1k 1%; R0805_Hand
R5, R6: 100k 1%; R0805_Hand
R7, R8: 10k 1%; R0805_Hand
U1, U2: OPA333AIDBVR; SOT23_5_Hand

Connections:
/3V3_IR: C6.1, J2.3, R6.2, U2.5
/3V3_RED: C5.1, J1.3, R5.2, U1.5
/FB_IR: C2.2, R2.2, R4.1, U2.1
/FB_RED: C1.2, R1.2, R3.1, U1.1
/GND_IR: C4.2, C6.2, C8.2, D2.2, J2.4, J3.4, R8.1, U2.2
/GND_RED: C3.2, C5.2, C7.2, D1.2, J1.4, J3.2, R7.1, U1.2
/OUT_IR: C8.1, J2.1, J3.3, R4.2
/OUT_RED: C7.1, J1.1, J3.1, R3.2
/SUM_IR: C2.1, D2.1, R2.1, U2.4
/SUM_RED: C1.1, D1.1, R1.1, U1.4
/VREF_IR: C4.1, R6.1, R8.2, U2.3
/VREF_RED: C3.1, R5.1, R7.2, U1.3

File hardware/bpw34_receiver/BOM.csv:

References,Value,Package,Qty,Notes
"D1,D2",BPW34,Vishay leaded top-view photodiode,2,Cathode-marked lead -> square K pad
"U1,U2",OPA333AIDBVR,SOT-23-5,2,MCP6001T-I/OT is a pin-compatible low-cost alternative
"R1,R2",1M 1%,0805,2,TIA feedback; reduce to 330k if output saturates
"C1,C2",22pF C0G/NP0 50V,0805,2,TIA stability capacitor
"R3,R4",1k 1%,0805,2,Output RC series resistor
"R5,R6",100k 1%,0805,2,VREF divider top
"R7,R8",10k 1%,0805,2,VREF divider bottom
"C3,C4",100nF X7R 25V,0805,2,VREF filter
"C7,C8",1uF X7R 16V,0805,2,Output RC capacitor after 1k resistor
"C5,C6",100nF X7R 25V,0805,2,Op-amp supply bypass
"J1,J2",1x4 male 2.00mm,THT vertical,2,Grove A2 RED and A0 IR
J3,1x4 male 2.54mm,THT vertical,1,"OUT_RED,GND_RED,OUT_IR,GND_IR"

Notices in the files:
README.md:
License: MIT
